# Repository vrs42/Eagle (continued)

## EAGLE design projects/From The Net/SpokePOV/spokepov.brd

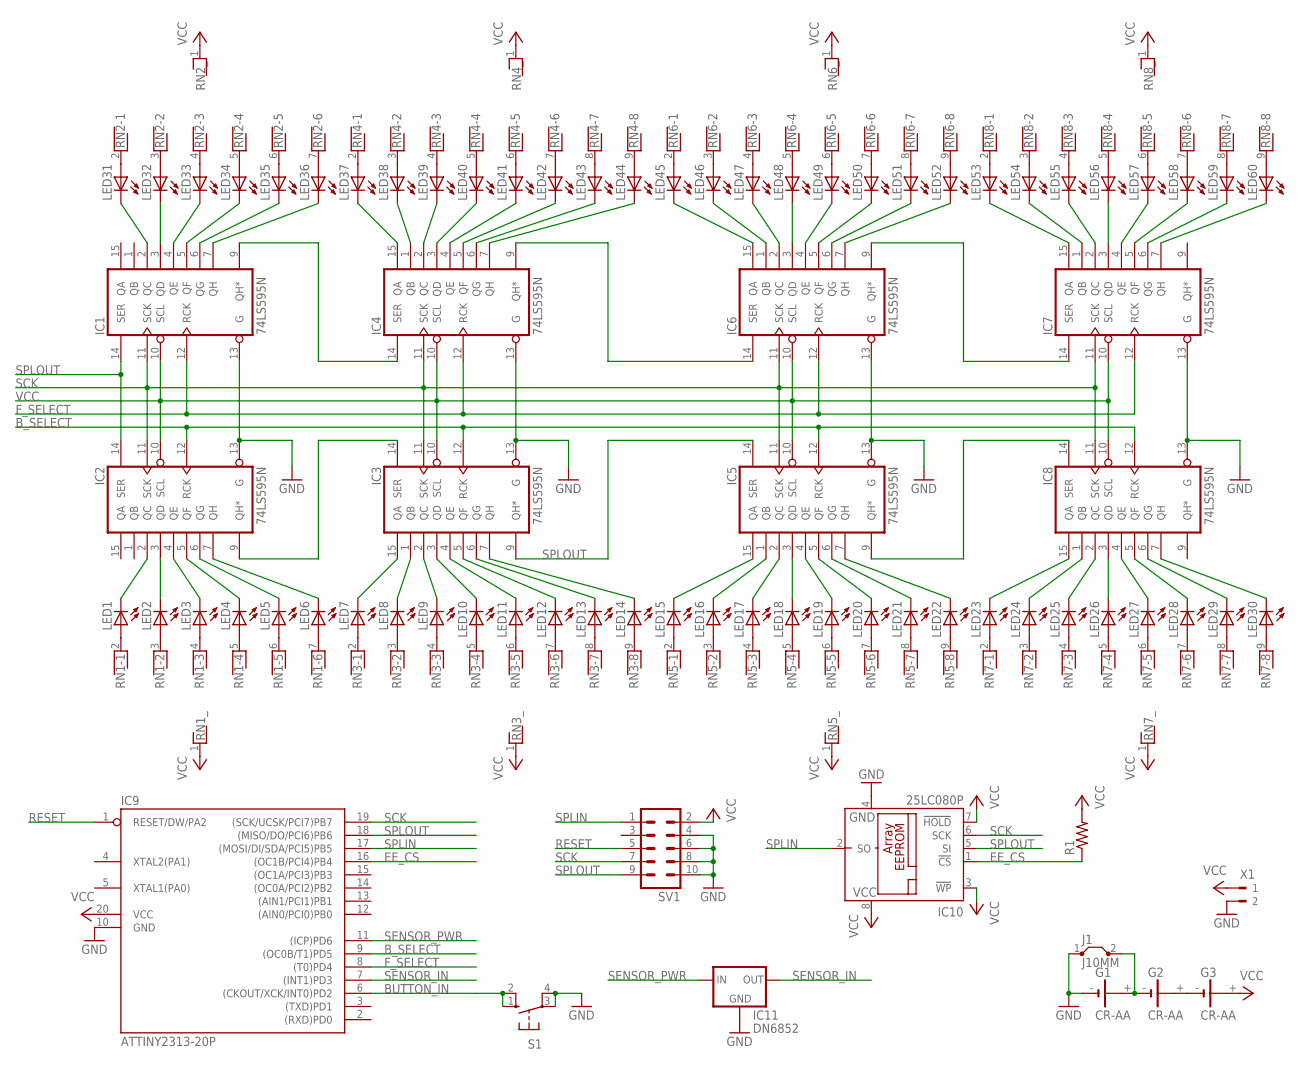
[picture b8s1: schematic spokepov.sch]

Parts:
G1, G2, G3: CR-AA; CRAA
IC1, IC2, IC3, IC4, IC5, IC6, IC7, IC8: 74LS595N; DIL16
IC9: ATTINY2313-20P; DIL20
IC10: 25LC080P; DIL8
IC11: DN6852; 78MXXS
J1: J10MM; 10
LED1, LED2, LED3, LED4, LED5, LED6, LED7, LED8, LED9, LED10, LED11, LED12, LED13, LED14, LED15, LED16, LED17, LED18, LED19, LED20, LED21, LED22, LED23, LED24, LED25, LED26, LED27, LED28, LED29, LED30, LED31, LED32, LED33, LED34, LED35, LED36, LED37, LED38, LED39, LED40, LED41, LED42, LED43, LED44, LED45, LED46, LED47, LED48, LED49, LED50, LED51, LED52, LED53, LED54, LED55, LED56, LED57, LED58, LED59, LED60: LED5MM
R1: R-US_0207/10; 0207/10
RN1, RN2, RN3, RN4, RN5, RN6, RN7, RN8: RNX8; RN-9
S1: 10-XX; B3F-10XX
SV1: ML10
X1: 90-2

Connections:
BUTTON_IN: IC9.6 ((CKOUT/XCK/INT0)PD2), S1.1 (S), S1.2 (S1)
B_SELECT: IC2.12 (RCK), IC3.12 (RCK), IC5.12 (RCK), IC8.12 (RCK), IC9.9 ((OC0B/T1)PD5)
EE_CS: IC9.16 ((OC1B/PCI4)PB4), IC10.1 (!CS), R1.1
F_SELECT: IC1.12 (RCK), IC4.12 (RCK), IC6.12 (RCK), IC7.12 (RCK), IC9.8 ((T0)PD4)
GND: G1.-, IC1.8 (GND), IC1.13 (G), IC2.8 (GND), IC2.13 (G), IC3.8 (GND), IC3.13 (G), IC4.8 (GND), IC4.13 (G), IC5.8 (GND), IC5.13 (G), IC6.8 (GND), IC6.13 (G), IC7.8 (GND), IC7.13 (G), IC8.8 (GND), IC8.13 (G), IC9.10 (GND), IC10.4 (GND), IC11.GND, J1.1, S1.3, S1.4 (P1), SV1.4, SV1.6, SV1.8, SV1.10, X1.2
unnamed: IC7.15 (QA), LED53.K (C)
unnamed: IC7.1 (QB), LED54.K (C)
unnamed: IC7.2 (QC), LED55.K (C)
unnamed: IC7.3 (QD), LED56.K (C)
unnamed: IC7.4 (QE), LED57.K (C)
unnamed: IC7.5 (QF), LED58.K (C)
unnamed: IC2.2 (QC), LED1.K (C)
unnamed: IC2.3 (QD), LED2.K (C)
unnamed: IC2.4 (QE), LED3.K (C)
unnamed: IC2.5 (QF), LED4.K (C)
unnamed: IC2.6 (QG), LED5.K (C)
unnamed: IC2.7 (QH), LED6.K (C)
unnamed: LED1.A, RN1.2
unnamed: LED2.A, RN1.3
unnamed: LED3.A, RN1.4
unnamed: LED4.A, RN1.5
unnamed: LED5.A, RN1.6
unnamed: LED6.A, RN1.7
unnamed: LED7.A, RN3.2
unnamed: LED8.A, RN3.3
unnamed: LED9.A, RN3.4
unnamed: LED10.A, RN3.5
unnamed: LED11.A, RN3.6
unnamed: LED12.A, RN3.7
unnamed: LED13.A, RN3.8
unnamed: LED14.A, RN3.9
unnamed: LED15.A, RN5.2
unnamed: LED16.A, RN5.3
unnamed: LED17.A, RN5.4
unnamed: LED18.A, RN5.5
unnamed: LED19.A, RN5.6
unnamed: LED20.A, RN5.7
unnamed: LED21.A, RN5.8
unnamed: LED22.A, RN5.9
unnamed: LED23.A, RN7.2
unnamed: LED24.A, RN7.3
unnamed: LED25.A, RN7.4
unnamed: LED26.A, RN7.5
unnamed: LED27.A, RN7.6
unnamed: LED28.A, RN7.7
unnamed: LED29.A, RN7.8
unnamed: LED30.A, RN7.9
unnamed: IC1.2 (QC), LED31.K (C)
unnamed: IC1.3 (QD), LED32.K (C)
unnamed: IC1.4 (QE), LED33.K (C)
unnamed: IC1.5 (QF), LED34.K (C)
unnamed: IC1.6 (QG), LED35.K (C)
unnamed: IC1.7 (QH), LED36.K (C)
unnamed: LED31.A, RN2.2
unnamed: LED32.A, RN2.3
unnamed: LED33.A, RN2.4
unnamed: LED34.A, RN2.5
unnamed: LED35.A, RN2.6
unnamed: LED36.A, RN2.7
unnamed: LED37.A, RN4.2
unnamed: LED38.A, RN4.3
unnamed: LED39.A, RN4.4
unnamed: LED40.A, RN4.5
unnamed: LED41.A, RN4.6
unnamed: LED42.A, RN4.7
unnamed: LED43.A, RN4.8
unnamed: LED44.A, RN4.9
unnamed: LED45.A, RN6.2
unnamed: LED46.A, RN6.3
unnamed: LED47.A, RN6.4
unnamed: LED48.A, RN6.5
unnamed: LED49.A, RN6.6
unnamed: LED50.A, RN6.7
unnamed: LED51.A, RN6.8
unnamed: LED52.A, RN6.9
unnamed: LED53.A, RN8.2
unnamed: LED54.A, RN8.3
unnamed: LED55.A, RN8.4
unnamed: LED56.A, RN8.5
unnamed: LED57.A, RN8.6
unnamed: LED58.A, RN8.7
unnamed: LED59.A, RN8.8
unnamed: LED60.A, RN8.9
unnamed: IC3.15 (QA), LED7.K (C)
unnamed: IC3.1 (QB), LED8.K (C)
unnamed: IC3.2 (QC), LED9.K (C)
unnamed: IC3.3 (QD), LED10.K (C)
unnamed: IC3.4 (QE), LED11.K (C)
unnamed: IC3.5 (QF), LED12.K (C)
unnamed: IC3.6 (QG), LED13.K (C)
unnamed: IC3.7 (QH), LED14.K (C)
unnamed: IC5.15 (QA), LED15.K (C)
unnamed: IC5.1 (QB), LED16.K (C)
unnamed: IC5.2 (QC), LED17.K (C)
unnamed: IC5.3 (QD), LED18.K (C)
unnamed: IC5.4 (QE), LED19.K (C)
unnamed: IC5.5 (QF), LED20.K (C)
unnamed: IC5.6 (QG), LED21.K (C)
unnamed: IC5.7 (QH), LED22.K (C)
unnamed: IC8.15 (QA), LED23.K (C)
unnamed: IC8.1 (QB), LED24.K (C)
unnamed: IC8.2 (QC), LED25.K (C)
unnamed: IC8.3 (QD), LED26.K (C)
unnamed: IC8.7 (QH), LED30.K (C)
unnamed: IC8.6 (QG), LED29.K (C)
unnamed: IC8.5 (QF), LED28.K (C)
unnamed: IC8.4 (QE), LED27.K (C)
unnamed: IC7.6 (QG), LED59.K (C)
unnamed: IC7.7 (QH), LED60.K (C)
unnamed: IC6.7 (QH), LED52.K (C)
unnamed: IC6.15 (QA), LED45.K (C)
unnamed: IC6.1 (QB), LED46.K (C)
unnamed: IC6.2 (QC), LED47.K (C)
unnamed: IC6.3 (QD), LED48.K (C)
unnamed: IC6.4 (QE), LED49.K (C)
unnamed: IC6.5 (QF), LED50.K (C)
unnamed: IC6.6 (QG), LED51.K (C)
unnamed: IC4.15 (QA), LED37.K (C)
unnamed: IC4.1 (QB), LED38.K (C)
unnamed: IC4.2 (QC), LED39.K (C)
unnamed: IC4.3 (QD), LED40.K (C)
unnamed: IC4.4 (QE), LED41.K (C)
unnamed: IC4.5 (QF), LED42.K (C)
unnamed: IC4.6 (QG), LED43.K (C)
unnamed: IC4.7 (QH), LED44.K (C)
unnamed: G1.+, G2.-, J1.2
unnamed: IC1.9 (QH*), IC4.14 (SER)
unnamed: IC2.9 (QH*), IC3.14 (SER)
unnamed: IC5.9 (QH*), IC8.14 (SER)
unnamed: IC4.9 (QH*), IC6.14 (SER)
unnamed: G2.+, G3.-
unnamed: IC6.9 (QH*), IC7.14 (SER)
RESET: IC9.1 (RESET/DW/PA2), SV1.5
SCK: IC1.11 (SCK), IC2.11 (SCK), IC3.11 (SCK), IC4.11 (SCK), IC5.11 (SCK), IC6.11 (SCK), IC7.11 (SCK), IC8.11 (SCK), IC9.19 ((SCK/UCSK/PCI7)PB7), IC10.6 (SCK), SV1.7
SENSOR_IN: IC9.7 ((INT1)PD3), IC11.OUT
SENSOR_PWR: IC9.11 ((ICP)PD6), IC11.IN
SPLIN: IC9.17 ((MOSI/DI/SDA/PCI5)PB5), IC10.2 (SO), SV1.1
SPLOUT: IC1.14 (SER), IC2.14 (SER), IC3.9 (QH*), IC5.14 (SER), IC9.18 ((MISO/DO/PCI6)PB6), IC10.5 (SI), SV1.9
VCC: G3.+, IC1.10 (SCL), IC1.16 (VCC), IC2.10 (SCL), IC2.16 (VCC), IC3.10 (SCL), IC3.16 (VCC), IC4.10 (SCL), IC4.16 (VCC), IC5.10 (SCL), IC5.16 (VCC), IC6.10 (SCL), IC6.16 (VCC), IC7.10 (SCL), IC7.16 (VCC), IC8.10 (SCL), IC8.16 (VCC), IC9.20 (VCC), IC10.3 (!WP), IC10.7 (!HOLD), IC10.8 (VCC), R1.2, RN1.1, RN2.1, RN3.1, RN4.1, RN5.1, RN6.1, RN7.1, RN8.1, SV1.2, X1.1

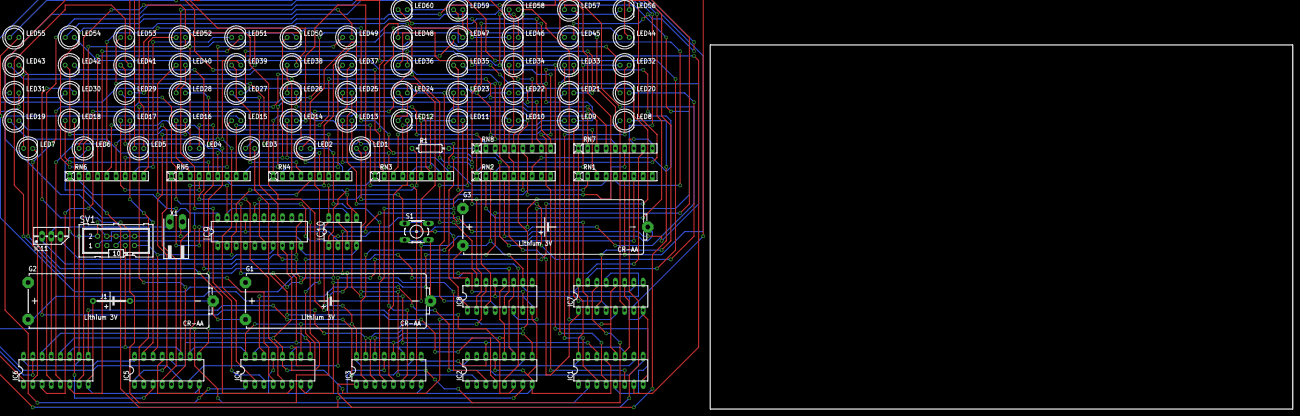
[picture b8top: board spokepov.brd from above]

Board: 2 copper layers, 160.0 x 100.0 mm, 87 parts (0 on the bottom side), 139 nets.
